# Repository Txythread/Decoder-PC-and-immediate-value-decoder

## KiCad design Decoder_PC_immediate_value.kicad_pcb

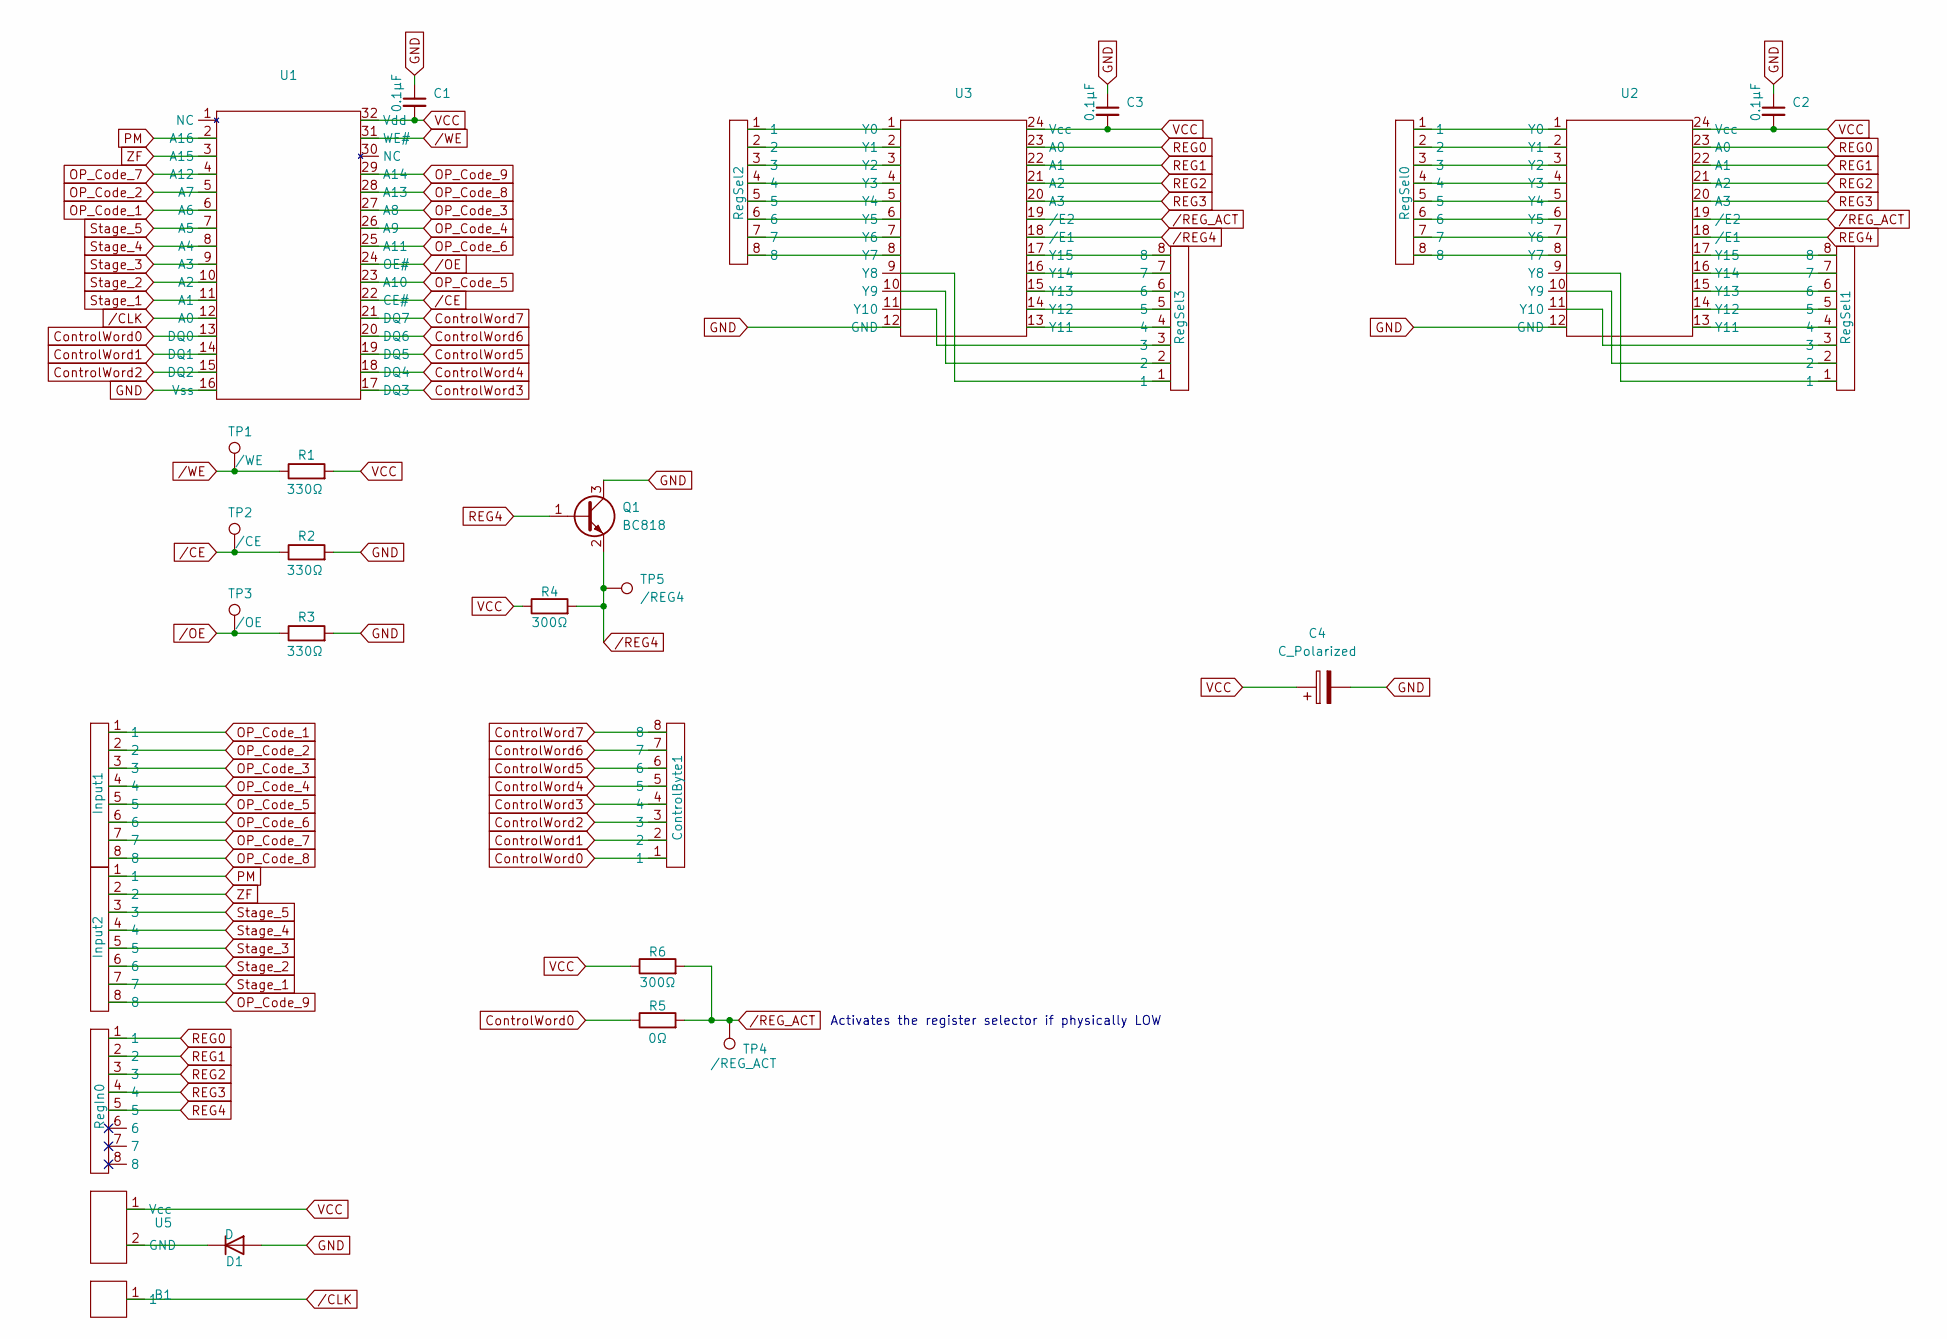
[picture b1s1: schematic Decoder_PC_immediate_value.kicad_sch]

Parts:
B1: Single Bit Bus
C1, C2, C3: 0.1µF; C_0805_2012Metric_Pad1.18x1.45mm_HandSolder
C4: C_Polarized; CP_Radial_D6.3mm_P2.50mm
ControlByte1: 8 Bit Bus Small
D1: D; D_5W_P10.16mm_Horizontal
Input1, Input2: 8 Bit Bus Small
Q1: BC818; SOT-23
R1, R2, R3: 330Ω; R_0805_2012Metric_Pad1.20x1.40mm_HandSolder
R4, R6: 300Ω; R_0805_2012Metric_Pad1.20x1.40mm_HandSolder
R5: 0Ω; R_0805_2012Metric_Pad1.20x1.40mm_HandSolder
RegIn0: 8 Bit Bus Small
RegSel0, RegSel1, RegSel2, RegSel3: 8 Bit Bus Small
TP1: /WE; TestPoint_Pad_D1.0mm
TP2: /CE; TestPoint_Pad_D1.0mm
TP3: /OE; TestPoint_Pad_D1.0mm
TP4: /REG_ACT; TestPoint_Pad_D1.0mm
TP5: /REG4; TestPoint_Pad_D1.0mm
U1: PLCC-32_11.4x14.0mm_P1.27mm
U2, U3: SOIC-24W_7.5x15.4mm_P1.27mm
U5: Vcc & GND

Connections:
ControlWord0: ControlByte1.1, R5.1, U1.13 (DQ0)
ControlWord1: ControlByte1.2, U1.14 (DQ1)
ControlWord2: ControlByte1.3, U1.15 (DQ2)
ControlWord3: ControlByte1.4, U1.17 (DQ3)
ControlWord4: ControlByte1.5, U1.18 (DQ4)
ControlWord5: ControlByte1.6, U1.19 (DQ5)
ControlWord6: ControlByte1.7, U1.20 (DQ6)
ControlWord7: ControlByte1.8, U1.21 (DQ7)
GND: C1.1, C2.1, C3.1, C4.2, D1.2 (A), Q1.3 (C), R2.2, R3.2, U1.16 (Vss), U2.12 (GND), U3.12 (GND)
unnamed: D1.1 (K), U5.2 (GND)
unnamed: RegSel0.1, U2.1 (Y0)
unnamed: RegSel0.2, U2.2 (Y1)
unnamed: RegSel0.3, U2.3 (Y2)
unnamed: RegSel0.4, U2.4 (Y3)
unnamed: RegSel0.5, U2.5 (Y4)
unnamed: RegSel0.6, U2.6 (Y5)
unnamed: RegSel0.7, U2.7 (Y6)
unnamed: RegSel0.8, U2.8 (Y7)
unnamed: RegSel1.1, U2.9 (Y8)
unnamed: RegSel1.2, U2.10 (Y9)
unnamed: RegSel1.3, U2.11 (Y10)
unnamed: RegSel1.4, U2.13 (Y11)
unnamed: RegSel1.5, U2.14 (Y12)
unnamed: RegSel1.6, U2.15 (Y13)
unnamed: RegSel1.7, U2.16 (Y14)
unnamed: RegSel1.8, U2.17 (Y15)
unnamed: RegSel2.1, U3.1 (Y0)
unnamed: RegSel2.2, U3.2 (Y1)
unnamed: RegSel2.3, U3.3 (Y2)
unnamed: RegSel2.4, U3.4 (Y3)
unnamed: RegSel2.5, U3.5 (Y4)
unnamed: RegSel2.6, U3.6 (Y5)
unnamed: RegSel2.7, U3.7 (Y6)
unnamed: RegSel2.8, U3.8 (Y7)
unnamed: RegSel3.1, U3.9 (Y8)
unnamed: RegSel3.2, U3.10 (Y9)
unnamed: RegSel3.3, U3.11 (Y10)
unnamed: RegSel3.4, U3.13 (Y11)
unnamed: RegSel3.5, U3.14 (Y12)
unnamed: RegSel3.6, U3.15 (Y13)
unnamed: RegSel3.7, U3.16 (Y14)
unnamed: RegSel3.8, U3.17 (Y15)
OP_Code_1: Input1.1, U1.6 (A6)
OP_Code_2: Input1.2, U1.5 (A7)
OP_Code_3: Input1.3, U1.27 (A8)
OP_Code_4: Input1.4, U1.26 (A9)
OP_Code_5: Input1.5, U1.23 (A10)
OP_Code_6: Input1.6, U1.25 (A11)
OP_Code_7: Input1.7, U1.4 (A12)
OP_Code_8: Input1.8, U1.28 (A13)
OP_Code_9: Input2.8, U1.29 (A14)
PM: Input2.1, U1.2 (A16)
REG0: RegIn0.1, U2.23 (A0), U3.23 (A0)
REG1: RegIn0.2, U2.22 (A1), U3.22 (A1)
REG2: RegIn0.3, U2.21 (A2), U3.21 (A2)
REG3: RegIn0.4, U2.20 (A3), U3.20 (A3)
REG4: Q1.1 (B), RegIn0.5, U2.18 (/E1)
Stage_1: Input2.7, U1.11 (A1)
Stage_2: Input2.6, U1.10 (A2)
Stage_3: Input2.5, U1.9 (A3)
Stage_4: Input2.4, U1.8 (A4)
Stage_5: Input2.3, U1.7 (A5)
VCC: C1.2, C2.2, C3.2, C4.1, R1.2, R4.1, R6.1, U1.32 (Vdd), U2.24 (Vcc), U3.24 (Vcc), U5.1 (Vcc)
ZF: Input2.2, U1.3 (A15)
/CE: R2.1, TP2.1, U1.22 (CE#)
/CLK: B1.1, U1.12 (A0)
/OE: R3.1, TP3.1, U1.24 (OE#)
/REG4: Q1.2 (E), R4.2, TP5.1, U3.18 (/E1)
/REG_ACT: R5.2, R6.2, TP4.1, U2.19 (/E2), U3.19 (/E2)
/WE: R1.1, TP1.1, U1.31 (WE#)

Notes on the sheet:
Activates the register selector if physically LOW

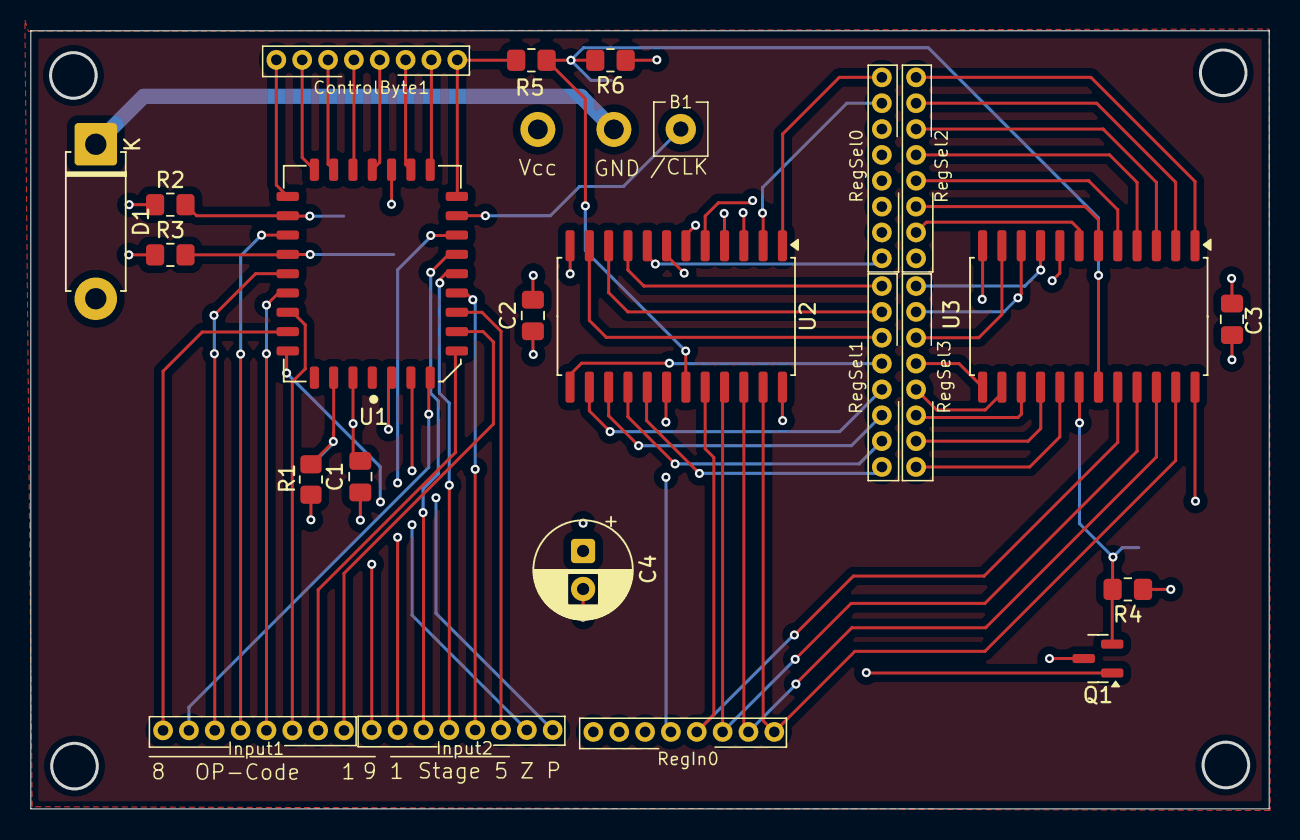
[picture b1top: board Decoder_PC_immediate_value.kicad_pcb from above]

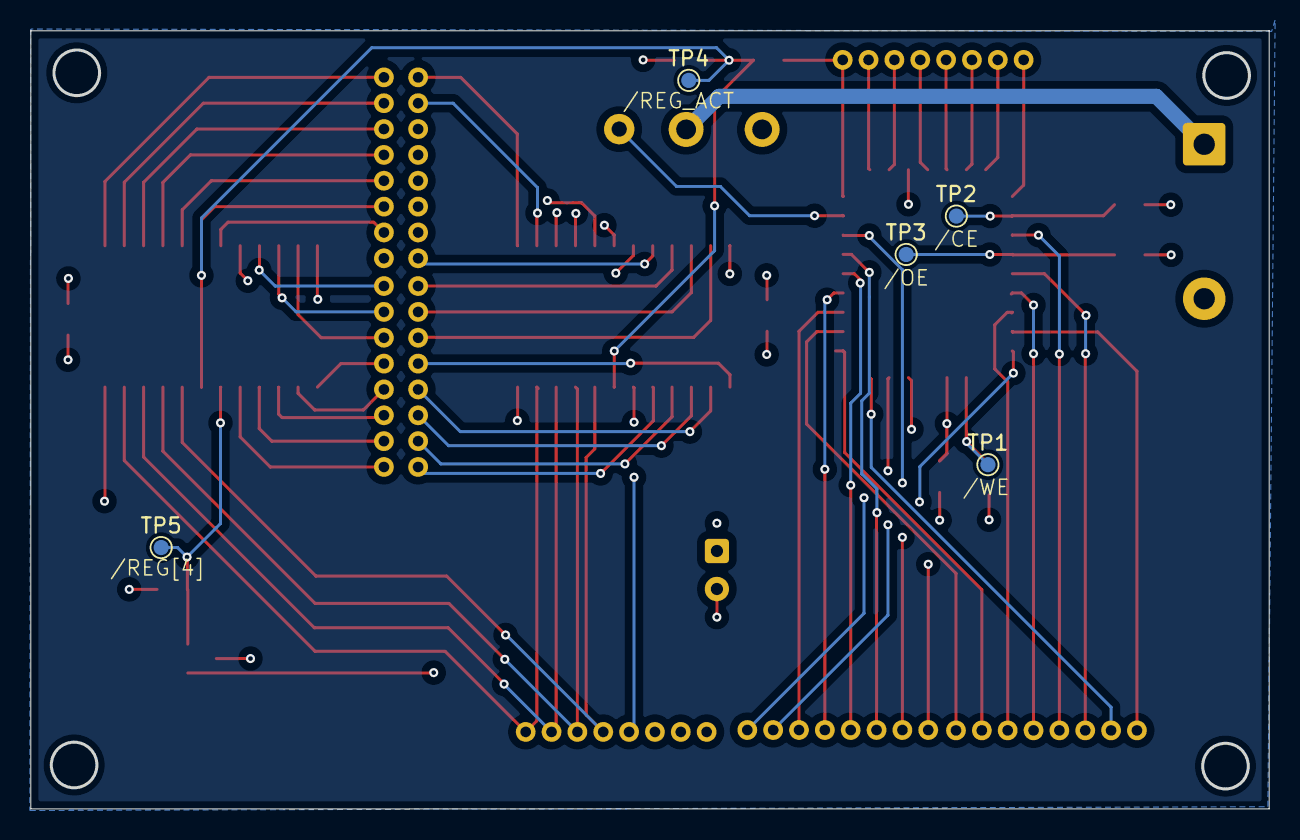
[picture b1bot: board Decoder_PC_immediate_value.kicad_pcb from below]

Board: 4 copper layers, 81.3 x 51.0 mm, 30 parts (5 on the bottom side), 70 nets.

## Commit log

2025-09-28 Added sample parts list
2025-09-28 Fixed formatting in part_list.md
2025-09-28 Added Gitignore
2025-09-28 Added storage flash
2025-09-28 Added /WE
2025-09-29 Added default pulls for /WE, /CE & /OE
2025-10-25 Some stuff for sure; idk can 't remember anymore
2025-10-25 Added Output for Control Byte
2025-10-25 Added Inputs for OP-Code
2025-10-26 Finished Decoder Design
2025-10-28 Added Decoder 1/2
2025-10-28 Schematic for Second Decoder
2025-10-28 Added Second Decoder
2025-10-28 Added Power Source
2025-10-28 Corrected Addressing Of Decoders
2025-10-28 Added Test Points
2025-11-02 Added Bulk Capacitor
2025-11-03 Corrected Position of Diode
